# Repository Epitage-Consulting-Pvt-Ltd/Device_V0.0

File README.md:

# Device_V0.0
Smart Employee Management Device

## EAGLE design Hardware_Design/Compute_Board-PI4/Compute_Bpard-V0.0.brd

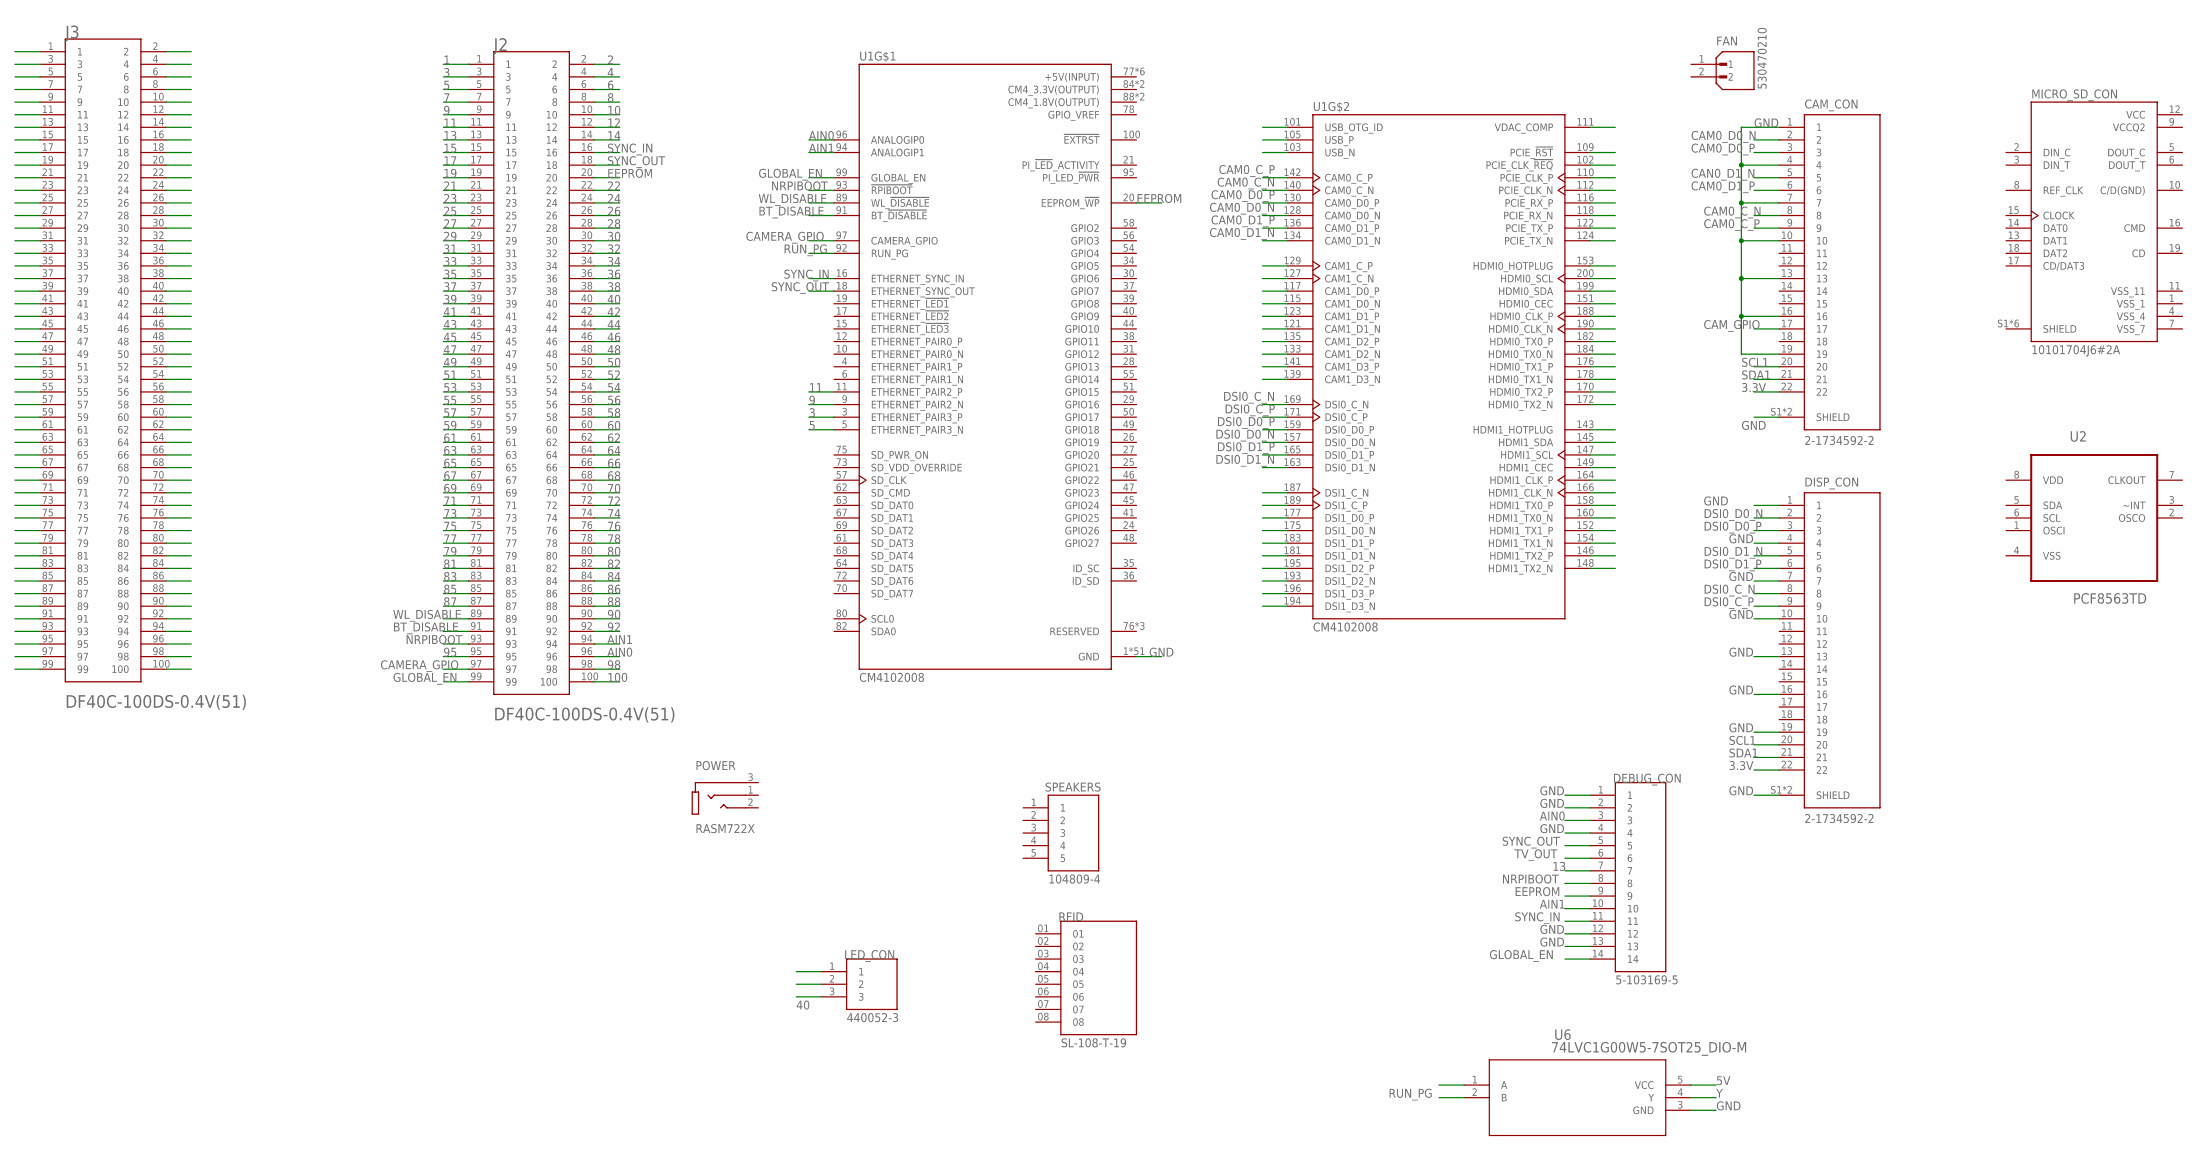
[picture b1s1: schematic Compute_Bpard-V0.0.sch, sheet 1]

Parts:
CAM_CON: 2-1734592-2; TE_2-1734592-2
DEBUG_CON: 5-103169-5; TE_5-103169-5
DISP_CON: 2-1734592-2; TE_2-1734592-2
FAN: 530470210; MOLEX_530470210
J2, J3: DF40C-100DS-0.4V(51); HRS_DF40C-100DS-0.4V(51)
LED_CON: 440052-3; TE_440052-3
MICRO_SD_CON: 10101704J6#2A; AMPHENOL_10101704J6#2A
POWER: RASM722X; SWITCHCRAFT_RASM722X
RFID: SL-108-T-19; SAMTEC_SL-108-T-19
SPEAKERS: 104809-4; TE_104809-4
U1: CM4102008; MODULE_CM4102008
U2: PCF8563TD; SOIC127P600X175-8N
U6: 74LVC1G00W5-7SOT25_DIO-M; SOT25_DIO-M

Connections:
1: J2.1
2: J2.2
3: J2.3, U1.3 (ETHERNET_PAIR3_P)
3.3V: CAM_CON.22, DISP_CON.22
4: J2.4
5: J2.5, U1.5 (ETHERNET_PAIR3_N)
5V: U6.5 (VCC)
6: J2.6
7: J2.7
8: J2.8
9: J2.9, U1.9 (ETHERNET_PAIR2_N)
10: J2.10
11: J2.11, U1.11 (ETHERNET_PAIR2_P)
12: J2.12
13: DEBUG_CON.7, J2.13
14: J2.14
15: J2.15
17: J2.17
19: J2.19
21: J2.21
22: J2.22
23: J2.23
24: J2.24
25: J2.25
26: J2.26
27: J2.27
28: J2.28
29: J2.29
30: J2.30
31: J2.31
32: J2.32
33: J2.33
34: J2.34
35: J2.35
36: J2.36
37: J2.37
38: J2.38
39: J2.39
40: J2.40, LED_CON.3
41: J2.41
42: J2.42
43: J2.43
44: J2.44
45: J2.45
46: J2.46
47: J2.47
48: J2.48
49: J2.49
50: J2.50
51: J2.51
52: J2.52
53: J2.53
54: J2.54
55: J2.55
56: J2.56
57: J2.57
58: J2.58
59: J2.59
60: J2.60
61: J2.61
62: J2.62
63: J2.63
64: J2.64
65: J2.65
66: J2.66
67: J2.67
68: J2.68
69: J2.69
70: J2.70
71: J2.71
72: J2.72
73: J2.73
74: J2.74
75: J2.75
76: J2.76
77: J2.77
78: J2.78
79: J2.79
80: J2.80
81: J2.81
82: J2.82
83: J2.83
84: J2.84
85: J2.85
86: J2.86
87: J2.87
88: J2.88
90: J2.90
92: J2.92
95: J2.95
98: J2.98
100: J2.100
+5V(INPUT): U1.77 (+5V(INPUT)), U1.79 (+5V(INPUT)), U1.81 (+5V(INPUT)), U1.83 (+5V(INPUT)), U1.85 (+5V(INPUT)), U1.87 (+5V(INPUT))
AIN0: DEBUG_CON.3, J2.96, U1.96 (ANALOGIP0)
AIN1: DEBUG_CON.10, J2.94, U1.94 (ANALOGIP1)
BT_DISABLE: J2.91, U1.91 (BT_!DISABLE)
CAM0_C_N: CAM_CON.8, U1.140 (CAM0_C_N)
CAM0_C_P: CAM_CON.9, U1.142 (CAM0_C_P)
CAM0_D0_N: CAM_CON.2, U1.128 (CAM0_D0_N)
CAM0_D0_P: CAM_CON.3, U1.130 (CAM0_D0_P)
CAM0_D1_N: U1.134 (CAM0_D1_N)
CAM0_D1_P: CAM_CON.6, U1.136 (CAM0_D1_P)
CAMERA_GPIO: J2.97, U1.97 (CAMERA_GPIO)
CAM_GPIO: CAM_CON.17
CAN0_D1_N: CAM_CON.5
CM4_1.8V(OUTPUT): U1.88 (CM4_1.8V(OUTPUT)), U1.90 (CM4_1.8V(OUTPUT))
CM4_3.3V(OUTPUT): U1.84 (CM4_3.3V(OUTPUT)), U1.86 (CM4_3.3V(OUTPUT))
DSI0_C_N: DISP_CON.8, U1.169 (DSI0_C_N)
DSI0_C_P: DISP_CON.9, U1.171 (DSI0_C_P)
DSI0_D0_N: DISP_CON.2, U1.157 (DSI0_D0_N)
DSI0_D0_P: DISP_CON.3, U1.159 (DSI0_D0_P)
DSI0_D1_N: DISP_CON.5, U1.163 (DSI0_D1_N)
DSI0_D1_P: DISP_CON.6, U1.165 (DSI0_D1_P)
EEPROM: DEBUG_CON.9, J2.20, U1.20 (EEPROM_!WP)
GLOBAL_EN: DEBUG_CON.14, J2.99, U1.99 (GLOBAL_EN)
GND: CAM_CON.1, CAM_CON.4, CAM_CON.7, CAM_CON.10, CAM_CON.13, CAM_CON.16, CAM_CON.19, CAM_CON.S1 (SHIELD), CAM_CON.S2 (SHIELD), DEBUG_CON.1, DEBUG_CON.2, DEBUG_CON.4, DEBUG_CON.12, DEBUG_CON.13, DISP_CON.1, DISP_CON.4, DISP_CON.7, DISP_CON.10, DISP_CON.13, DISP_CON.16, DISP_CON.19, DISP_CON.S1 (SHIELD), DISP_CON.S2 (SHIELD), U1.1 (GND), U1.2 (GND), U1.7 (GND), U1.8 (GND), U1.13 (GND), U1.14 (GND), U1.22 (GND), U1.23 (GND), U1.32 (GND), U1.33 (GND), U1.42 (GND), U1.43 (GND), U1.52 (GND), U1.53 (GND), U1.59 (GND), U1.60 (GND), U1.65 (GND), U1.66 (GND), U1.71 (GND), U1.74 (GND), U1.98 (GND), U1.107 (GND), U1.108 (GND), U1.113 (GND), U1.114 (GND), U1.119 (GND), U1.120 (GND), U1.125 (GND), U1.126 (GND), U1.131 (GND), U1.132 (GND), U1.137 (GND), U1.138 (GND), U1.144 (GND), U1.150 (GND), U1.155 (GND), U1.156 (GND), U1.161 (GND), U1.162 (GND), U1.167 (GND), U1.168 (GND), U1.173 (GND), U1.174 (GND), U1.179 (GND), U1.180 (GND), U1.185 (GND), U1.186 (GND), U1.191 (GND), U1.192 (GND), U1.197 (GND), U1.198 (GND), U6.3 (GND); also elsewhere on the board
GPIO_VREF: U1.78 (GPIO_VREF)
unnamed: U1.101 (USB_OTG_ID), U1.102 (PCIE_CLK_!REQ), U1.103 (USB_N), U1.105 (USB_P), U1.109 (PCIE_!RST), U1.110 (PCIE_CLK_P), U1.111 (VDAC_COMP), U1.112 (PCIE_CLK_N), U1.115 (CAM1_D0_N), U1.116 (PCIE_RX_P), U1.117 (CAM1_D0_P), U1.118 (PCIE_RX_N), U1.121 (CAM1_D1_N), U1.122 (PCIE_TX_P), U1.123 (CAM1_D1_P), U1.124 (PCIE_TX_N), U1.127 (CAM1_C_N), U1.129 (CAM1_C_P), U1.133 (CAM1_D2_N), U1.135 (CAM1_D2_P), U1.139 (CAM1_D3_N), U1.141 (CAM1_D3_P), U1.143 (HDMI1_HOTPLUG), U1.145 (HDMI1_SDA), U1.146 (HDMI1_TX2_P), U1.147 (HDMI1_SCL), U1.148 (HDMI1_TX2_N), U1.149 (HDMI1_CEC), U1.151 (HDMI0_CEC), U1.152 (HDMI1_TX1_P), U1.153 (HDMI0_HOTPLUG), U1.154 (HDMI1_TX1_N), U1.158 (HDMI1_TX0_P), U1.160 (HDMI1_TX0_N), U1.164 (HDMI1_CLK_P), U1.166 (HDMI1_CLK_N), U1.170 (HDMI0_TX2_P), U1.172 (HDMI0_TX2_N), U1.175 (DSI1_D0_N), U1.176 (HDMI0_TX1_P), U1.177 (DSI1_D0_P), U1.178 (HDMI0_TX1_N), U1.181 (DSI1_D1_N), U1.182 (HDMI0_TX0_P), U1.183 (DSI1_D1_P), U1.184 (HDMI0_TX0_N), U1.187 (DSI1_C_N), U1.188 (HDMI0_CLK_P), U1.189 (DSI1_C_P), U1.190 (HDMI0_CLK_N), U1.193 (DSI1_D2_N), U1.194 (DSI1_D3_N), U1.195 (DSI1_D2_P), U1.196 (DSI1_D3_P), U1.199 (HDMI0_SDA), U1.200 (HDMI0_SCL)
unnamed: J3.1, J3.3, J3.5, J3.7, J3.9, J3.11, J3.13, J3.15, J3.17, J3.19, J3.21
unnamed: J3.23, J3.25, J3.27, J3.29, J3.31, J3.33, J3.35, J3.37, J3.39, J3.41, J3.43
unnamed: J3.45, J3.47, J3.49, J3.51, J3.53, J3.55, J3.57, J3.59, J3.61, J3.63, J3.65
unnamed: J3.67, J3.69, J3.71, J3.73, J3.75, J3.77, J3.79, J3.81, J3.83, J3.85, J3.87
unnamed: J3.89, J3.91, J3.93, J3.95, J3.97, J3.99
NRPIBOOT: DEBUG_CON.8, J2.93, U1.93 (!RPIBOOT)
RUN_PG: U1.92 (RUN_PG), U6.2 (B)
SCL1: CAM_CON.20, DISP_CON.20
SDA1: CAM_CON.21, DISP_CON.21
SYNC_IN: DEBUG_CON.11, J2.16, U1.16 (ETHERNET_SYNC_IN)
SYNC_OUT: DEBUG_CON.5, J2.18, U1.18 (ETHERNET_SYNC_OUT)
TV_OUT: DEBUG_CON.6
VCC: MICRO_SD_CON.12 (VCC); also elsewhere on the board
VCCQ2: MICRO_SD_CON.9 (VCCQ2)
VDD: U2.8 (VDD)
VSS: U2.4 (VSS); also elsewhere on the board
VSS_1: MICRO_SD_CON.1 (VSS_1)
VSS_4: MICRO_SD_CON.4 (VSS_4)
VSS_7: MICRO_SD_CON.7 (VSS_7)
VSS_11: MICRO_SD_CON.11 (VSS_11)
WL_DISABLE: J2.89, U1.89 (WL_!DISABLE)
Y: U6.4 (Y)

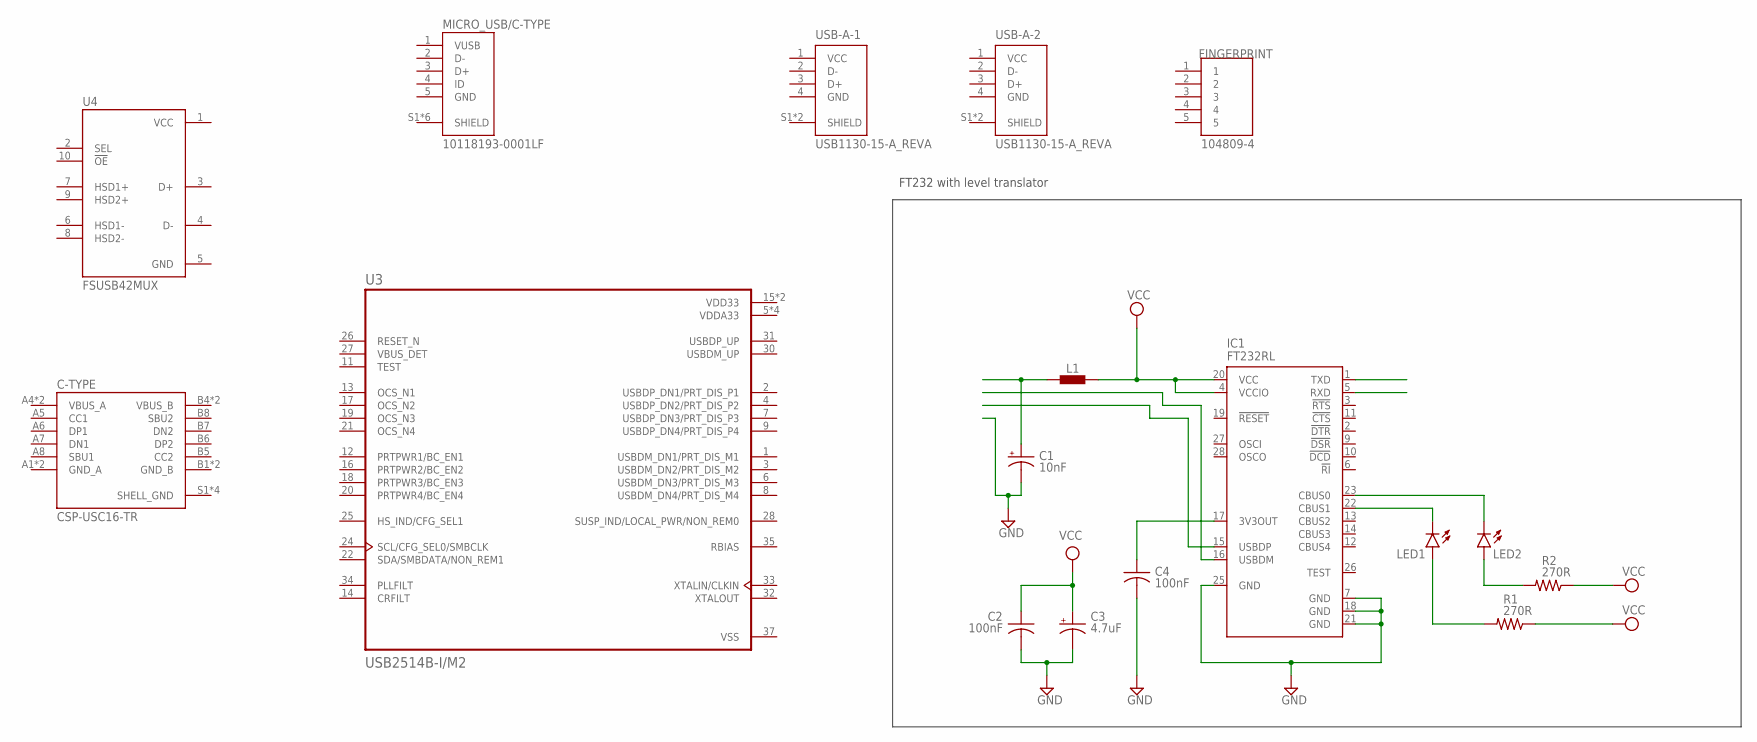
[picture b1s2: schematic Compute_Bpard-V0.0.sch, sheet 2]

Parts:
C1: 10nF; 085CS_1AR
C2, C4: 100nF; C025-024X044
C3: 4.7uF; 085CS_1AR
C-TYPE: CSP-USC16-TR; VALCON_CSP-USC16-TR
FINGERPRINT: 104809-4; TE_104809-4
IC1: FT232RL; SSOP28
L1: BLM15HB121SN1; 0402
LED1, LED2: LEDSMT1206; 1206
MICRO_USB/C-TYPE: 10118193-0001LF; FCI_10118193-0001LF
R1, R2: 270R; 0204V
U3: USB2514B-I/M2; QFN50P600X600X100-37N
U4: FSUSB42MUX; SOP50P490X110-10N
USB-A-1, USB-A-2: USB1130-15-A_REVA; GCT_USB1130-15-A_REVA

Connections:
GND: C1.-, C2.2, C3.-, C4.2, IC1.7 (GND), IC1.18 (GND), IC1.21 (GND), IC1.25 (GND), U4.5 (GND), USB-A-1.4 (GND), USB-A-2.4 (GND); also elsewhere on the board
GND_A: C-TYPE.A1 (GND_A), C-TYPE.A12 (GND_A)
GND_B: C-TYPE.B1 (GND_B), C-TYPE.B12 (GND_B)
unnamed: C1.+, L1.1
unnamed: C4.1, IC1.17 (3V3OUT)
unnamed: LED2.A, R2.2
unnamed: LED1.A, R1.2
unnamed: IC1.23 (CBUS0), LED2.C
unnamed: IC1.22 (CBUS1), LED1.C
SHELL_GND: C-TYPE.S1 (SHELL_GND), C-TYPE.S2 (SHELL_GND), C-TYPE.S3 (SHELL_GND), C-TYPE.S4 (SHELL_GND)
VBUS_A: C-TYPE.A4 (VBUS_A), C-TYPE.A9 (VBUS_A)
VBUS_B: C-TYPE.B4 (VBUS_B), C-TYPE.B9 (VBUS_B)
VCC: C2.1, C3.+, IC1.4 (VCCIO), IC1.20 (VCC), L1.2, R1.1, R2.1, U4.1 (VCC), USB-A-1.1 (VCC), USB-A-2.1 (VCC); also elsewhere on the board
VDD33: U3.15 (VDD33), U3.23 (VDD33)
VDDA33: U3.5 (VDDA33), U3.10 (VDDA33), U3.29 (VDDA33), U3.36 (VDDA33)
VSS: U3.37 (VSS); also elsewhere on the board

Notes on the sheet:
FT232 with level translator

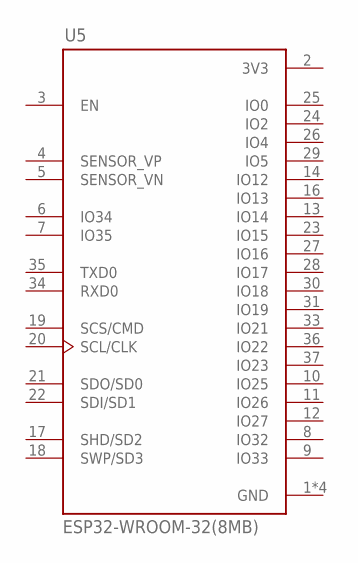
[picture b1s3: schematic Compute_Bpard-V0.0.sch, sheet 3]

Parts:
U5: ESP32-WROOM-32(8MB); MODULE_ESP32-WROOM-32(8MB)

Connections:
3V3: U5.2 (3V3)
GND: U5.1 (GND), U5.15 (GND), U5.38 (GND), U5.39 (GND); also elsewhere on the board

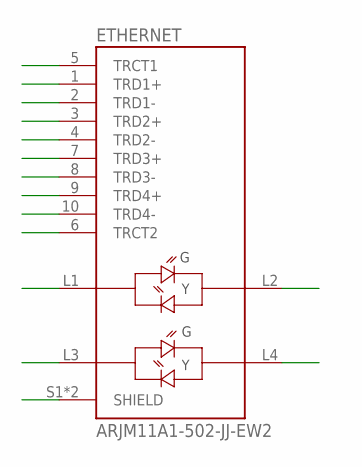
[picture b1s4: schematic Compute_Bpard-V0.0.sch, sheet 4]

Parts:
ETHERNET: ARJM11A1-502-JJ-EW2; ABRACON_ARJM11A1-502-JJ-EW2

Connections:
unnamed: ETHERNET.S1 (SHIELD), ETHERNET.S2 (SHIELD)

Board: 2 copper layers, 33 parts (10 on the bottom side), 57 nets, no tracks yet.

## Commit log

2023-03-14 Create Firmware
2023-03-14 Create Database
2023-03-14 Create UI_UX
2023-03-14 Create Hardware Design
2023-03-14 Update Firmware
2023-03-14 Update Database
2023-03-14 Create PCB
2023-03-14 Create Design
2023-03-14 Update issue templates
2023-03-27 Testing_Integration
2023-03-27 First_display Testing (functional_grid_testing.py)
2023-03-28 SplashScreen-testing snippet
2023-04-05 More Testing
2023-04-05 More-Testing
2023-04-06 Functioning Prototype in UI-UX/Ui_Testing/FunctioningFlow
2023-04-07 Theme-edit-testing
2023-04-10 FactoryCompliance + theme.py setup
2023-04-12 Create face_rec
2023-04-12 Committer: root <root@pi> On branch Main Your branch is up to date with 'origin/Main'.
    Changes to be committed:
    deleted: picam_v2.1/attendance/Attendance_2019-08-22_00-38-17.csv
    deleted: picam_v2.1/attendance/Attendance_2019-08-24_13-34-43.csv
    deleted: picam_v2.1/automail.txt
    deleted: picam_v2.1/captureimage.py.py
    deleted: picam_v2.1/checkcamera.py
2023-04-12 Committer: root <root@pi> On branch Main Your branch is up to date with 'origin/Main'. Changes to be committed: new file: Device_Firmware/FRAS1/Attendance/Attendance_2019-08-22_00-38-17.csv new file: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
2023-04-12 cleanup
2023-04-12 cleanupv2
2023-04-13 Directory changes for final
2023-04-14 SQL+Python ComplianceCheck
2023-04-17 RFID addition
2023-04-17 RFID addition + rfid-test
2023-04-19 TOPBand Test
2023-04-19 RFID_test
2023-04-19 new file: Device_Firmware/MFRC522/SPI-Py new file: Device_Firmware/pi-rfid/read.py new file: Device_Firmware/pi-rfid/write.py
2023-04-20 DB+Tables+punchverification+basicCRUD+
2023-04-29 basic
2023-04-30 close splashscreen.py once the menu button is clicked
2023-05-02 RFID_test_Hardware Testing
2023-05-02 comment add
2023-05-02 RFID_test_Hardware Testing-editv1
2023-05-02 modified: ../RFID-UI-Test/rfidUI.py
2023-05-05 modified: ../../UI-UX/IntegratedPrototype/Prototype1/AddUser_Working.py modified: ../../UI-UX/Ui_Testing/FunctioningFlow/AddUser_Working.py deleted: ../../UI-UX/Ui_Testing/FunctioningFlow/AddUser_Wor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
2023-05-05 new file: Device_Firmware/pi-rfid/RFIDDummy.py new file: Device_Firmware/pi-rfid/RFIDDummy.py.save new file: Device_Firmware/pi-rfid/error-int.txt new file: Device_Firmware/pi-rfid/rfid-19032023.py n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
2023-05-05 Indentation-error removed with deletion of fingerprint
2023-05-06 new file: Device_V0.1/proto1/AddUser_Working.py
2023-05-06 Setting the RFID number to the card number
2023-05-06 new file: Device_V0.1/proto1/__pycache__/AddUser_Working.cpython-39.pyc new file: Device_V0.1/proto1/__pycache__/EditUser.cpython-39.pyc new file: Device_V0.1/proto1/__pycache__/MenuGrid.cpython-39.p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
2023-05-06 modified: AddUser_Working.py
2023-05-06 modified: Device_V0.1/proto1/AddUser_Working.py modified: Device_V0.1/proto1/ViewUser_Working.py modified: Device_V0.1/proto1/__pycache__/AddUser_Working.cpython-39.pyc modified: Device_V0.1/proto1/_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
2023-05-08 ViewUser_Working.py connection back to UserMain_Working.py
2023-05-12 Alignment correction done
2023-05-12 color change done in theme.py top band added to splashscreen.py UserMain_Working.py entire form updated and working
2023-05-12 Entire UserMain_Working.py has been designed according to excel
2023-05-18 new file: Device_V0.1/proto1/src/card-verification-ui.py
2023-05-18 matchbox-keyboard-test
2023-05-19 renamed: Device_V0.1/proto1/src/card-verification-ui.py -> Device_V0.1/proto1/src/1-card-verification-ui.py new file: Device_V0.1/proto1/src/adduser-rfid-restrict-duplpication.py deleted: Device_V0.1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
2023-05-20 new file: Device_V0.1/proto1/src/keyboard-UI.py
2023-05-20 deleted: Device_V0.1/proto1/.AddUser_Working.py.swp deleted: Device_V0.1/proto1/epitage.csv deleted: Device_V0.1/proto1/move-files/AddUser_Working.py deleted: Device_V0.1/proto1/src/AddUser_Working.p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
2023-05-20 keyboard addition + housekeeping
2023-05-20 New screen addition (splash + menu + user reg + card verification) + housekeeping.
2023-05-22 Cleanup + Addition of Desktop prototype for computer only testing
2023-05-24 UI Textboxes working in DesktopPrototype
2023-05-24 new file: .1-userinfgerui.py.swp new file: 1-userinfgerui.py new file: fingerui.py new file: userfingerui.py
2023-05-24 fingertest
2023-05-24 modified: userfingerui_rutvij.py
2023-05-25 modified: Device_V0.1/proto1/AddUser_Working.py new file: Device_V0.1/proto1/src/AddUser_Working.py
2023-05-25 modified: ../../../Device_V0.1/proto1/AddUser_Working.py modified: ../../../Device_V0.1/proto1/MenuGrid.py modified: ../../../Device_V0.1/proto1/ViewUser_Working.py modified: ../../../Device_V0.1/pro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
2023-05-25 back button addition
2023-05-25 editing
2023-05-25 edit
2023-05-25 edit2
2023-05-25 edit3
2023-05-25 Update MenuGrid.py
    Changing Layout to old form
2023-05-29 splashscreen-finalization
2023-05-30 V2-Files to pulled into the proto1folder
2023-06-01 V2-Update for Friday Demo.
2023-06-02 V3-testing
2023-06-05 new file: Device_V0.1/proto2/AddUser_Working.py new file: Device_V0.1/proto2/EditUser.py new file: Device_V0.1/proto2/Epitage.png new file: Device_V0.1/proto2/MenuGrid_V2.py new file: Device_V0.1/pro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
2023-06-05 modified: Device_V0.1/proto2/MenuGrid_V2.py modified: Device_V0.1/proto2/UserMain_Final.py modified: Device_V0.1/proto2/__pycache__/MenuGrid_V2.cpython-39.pyc modified: Device_V0.1/proto2/__pycache__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
2023-06-10 V4 (CURRENT WORKING DIRECTORY)
2023-06-10 keyboard-testing
2023-06-15 prototype-testing
2023-06-19 Testing_Piagioo
2023-06-20 Testing_Piagioo-V2
2023-06-20 Testing_Piagioo-V3
2023-06-21 minor-correction
2023-06-21 modified: Device_V0.1/proto3/splashscreenv4.py
2023-06-21 minor-correction-v2
2023-06-21 minor-correction-v3
2023-06-22 new file: fingerverify.py
2023-06-22 new file: userverification.py
2023-06-22 minor-correction-v4
2023-06-22 minor-correction-v5+card verification
2023-06-22 minor-correction-v6
2023-06-22 minor-correction-v7
2023-06-22 new file: NewUserV4.py modified: UserMenu.py
2023-07-03 keyboard-testing-2
2023-07-03 keyboard-testing-3
2023-07-07 keyboard-testing-4
2023-07-11 requirements file
2023-07-12 new file: Device_Firmware/GT521F52/deletefps.py new file: Device_Firmware/network-parameters/networkUI.py new file: Device_Firmware/network-parameters/wifi-UI.py new file: Device_Firmware/network-par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

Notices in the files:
parts and their libraries:
COPYRIGHT: Copyright (C) 2023 Ultra Librarian. All rights reserved.
